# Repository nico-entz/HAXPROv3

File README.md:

# HAXPROv3
RTTY-Decoder-Software: dl-fldigi / https://ukhas.org.uk/doku.php?id=projects:dl-fldigi

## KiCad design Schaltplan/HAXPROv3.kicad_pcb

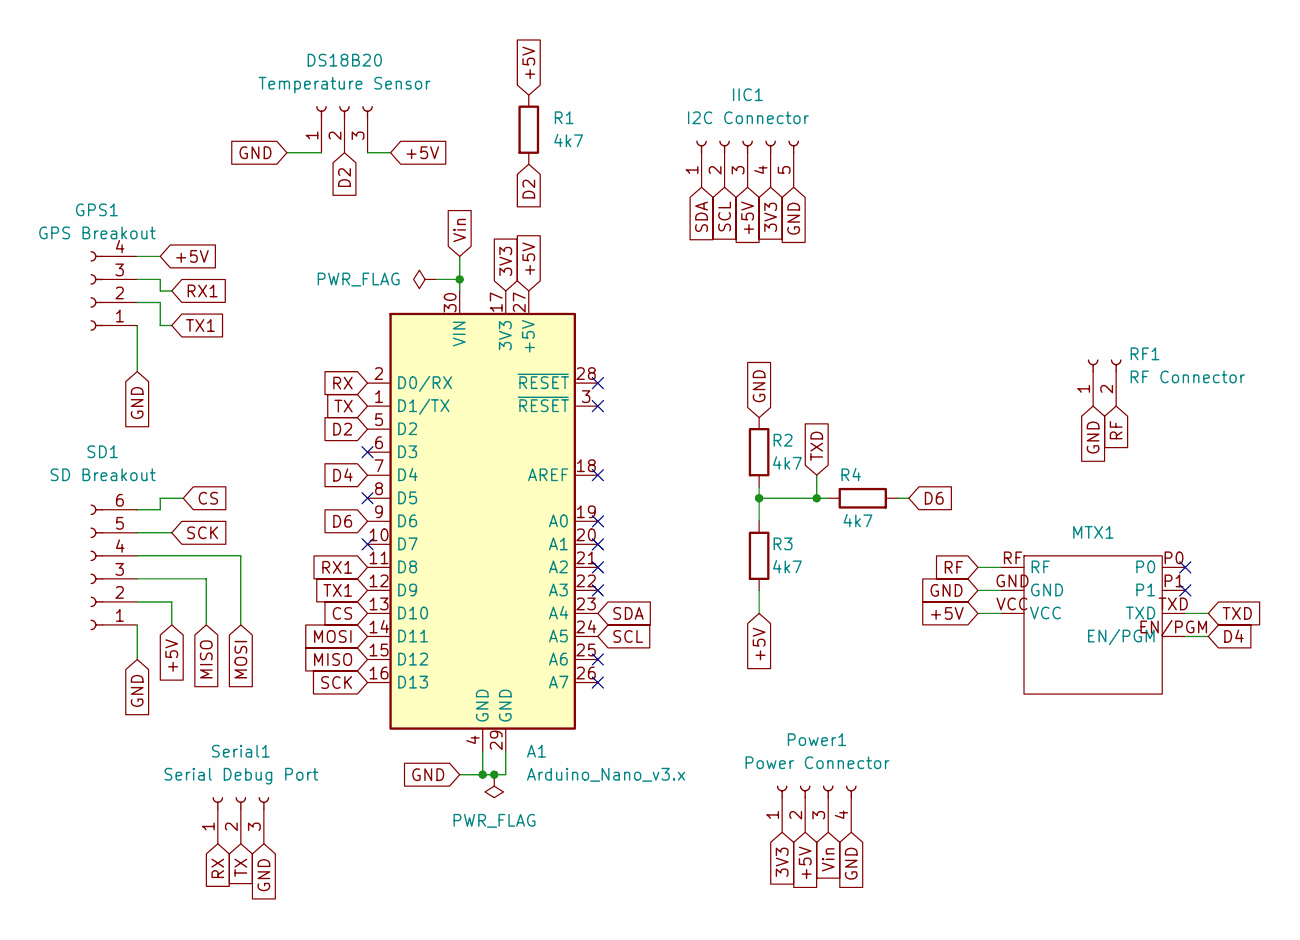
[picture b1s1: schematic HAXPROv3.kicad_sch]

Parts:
A1: Arduino_Nano_v3.x; Arduino_Nano
DS18B20: Temperature Sensor; PinSocket_1x03_P2.54mm_Vertical
GPS1: GPS Breakout; PinSocket_1x04_P2.54mm_Vertical
IIC1: I2C Connector; PinHeader_1x05_P2.54mm_Vertical
MTX1: MTX2
Power1: Power Connector; PinSocket_1x04_P2.54mm_Vertical
R1, R2, R3, R4: 4k7; R_Box_L14.0mm_W5.0mm_P9.00mm
RF1: RF Connector; PinHeader_1x02_P2.54mm_Vertical
SD1: SD Breakout; PinSocket_1x06_P2.54mm_Vertical
Serial1: Serial Debug Port; PinSocket_1x03_P2.54mm_Vertical

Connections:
3V3: A1.17 (3V3), IIC1.4, Power1.1
+5V: A1.27 (+5V), DS18B20.3, GPS1.4, IIC1.3, MTX1.VCC, Power1.2, R1.1, R3.2, SD1.2
CS: A1.13 (D10), SD1.6
D2: A1.5 (D2), DS18B20.2, R1.2
D4: A1.7 (D4), MTX1.EN/PGM
D6: A1.9 (D6), R4.2
GND: A1.4 (GND), A1.29 (GND), DS18B20.1, GPS1.1, IIC1.5, MTX1.GND, Power1.4, R2.1, RF1.1, SD1.1, Serial1.3
MISO: A1.15 (D12), SD1.3
MOSI: A1.14 (D11), SD1.4
RF: MTX1.RF, RF1.2
RX: A1.2 (D0/RX), Serial1.1
RX1: A1.11 (D8), GPS1.3
SCK: A1.16 (D13), SD1.5
SCL: A1.24 (A5), IIC1.2
SDA: A1.23 (A4), IIC1.1
TX: A1.1 (D1/TX), Serial1.2
TX1: A1.12 (D9), GPS1.2
TXD: MTX1.TXD, R2.2, R3.1, R4.1
Vin: A1.30 (VIN), Power1.3

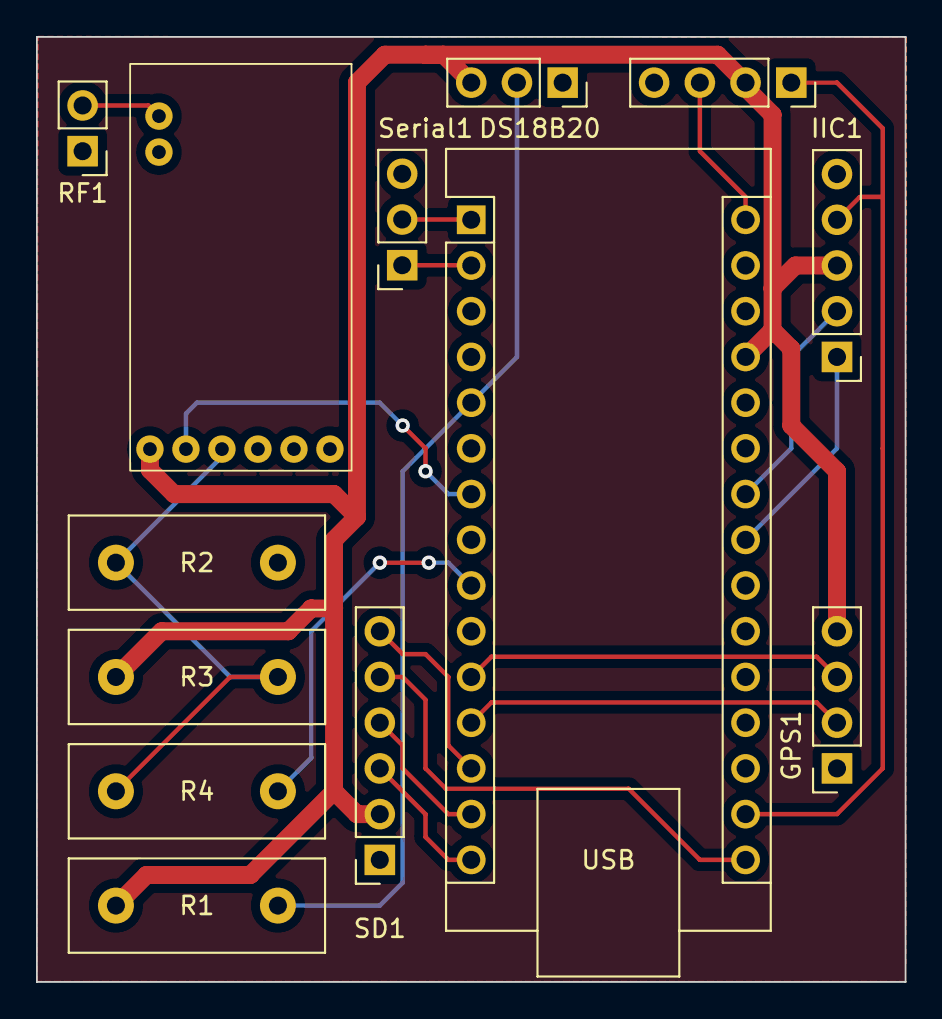
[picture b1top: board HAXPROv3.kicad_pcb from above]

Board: 2 copper layers, 48.3 x 52.5 mm, 13 parts (0 on the bottom side), 19 nets.

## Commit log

2024-12-28 added some documents
2024-12-28 added link to dl-fldigi
